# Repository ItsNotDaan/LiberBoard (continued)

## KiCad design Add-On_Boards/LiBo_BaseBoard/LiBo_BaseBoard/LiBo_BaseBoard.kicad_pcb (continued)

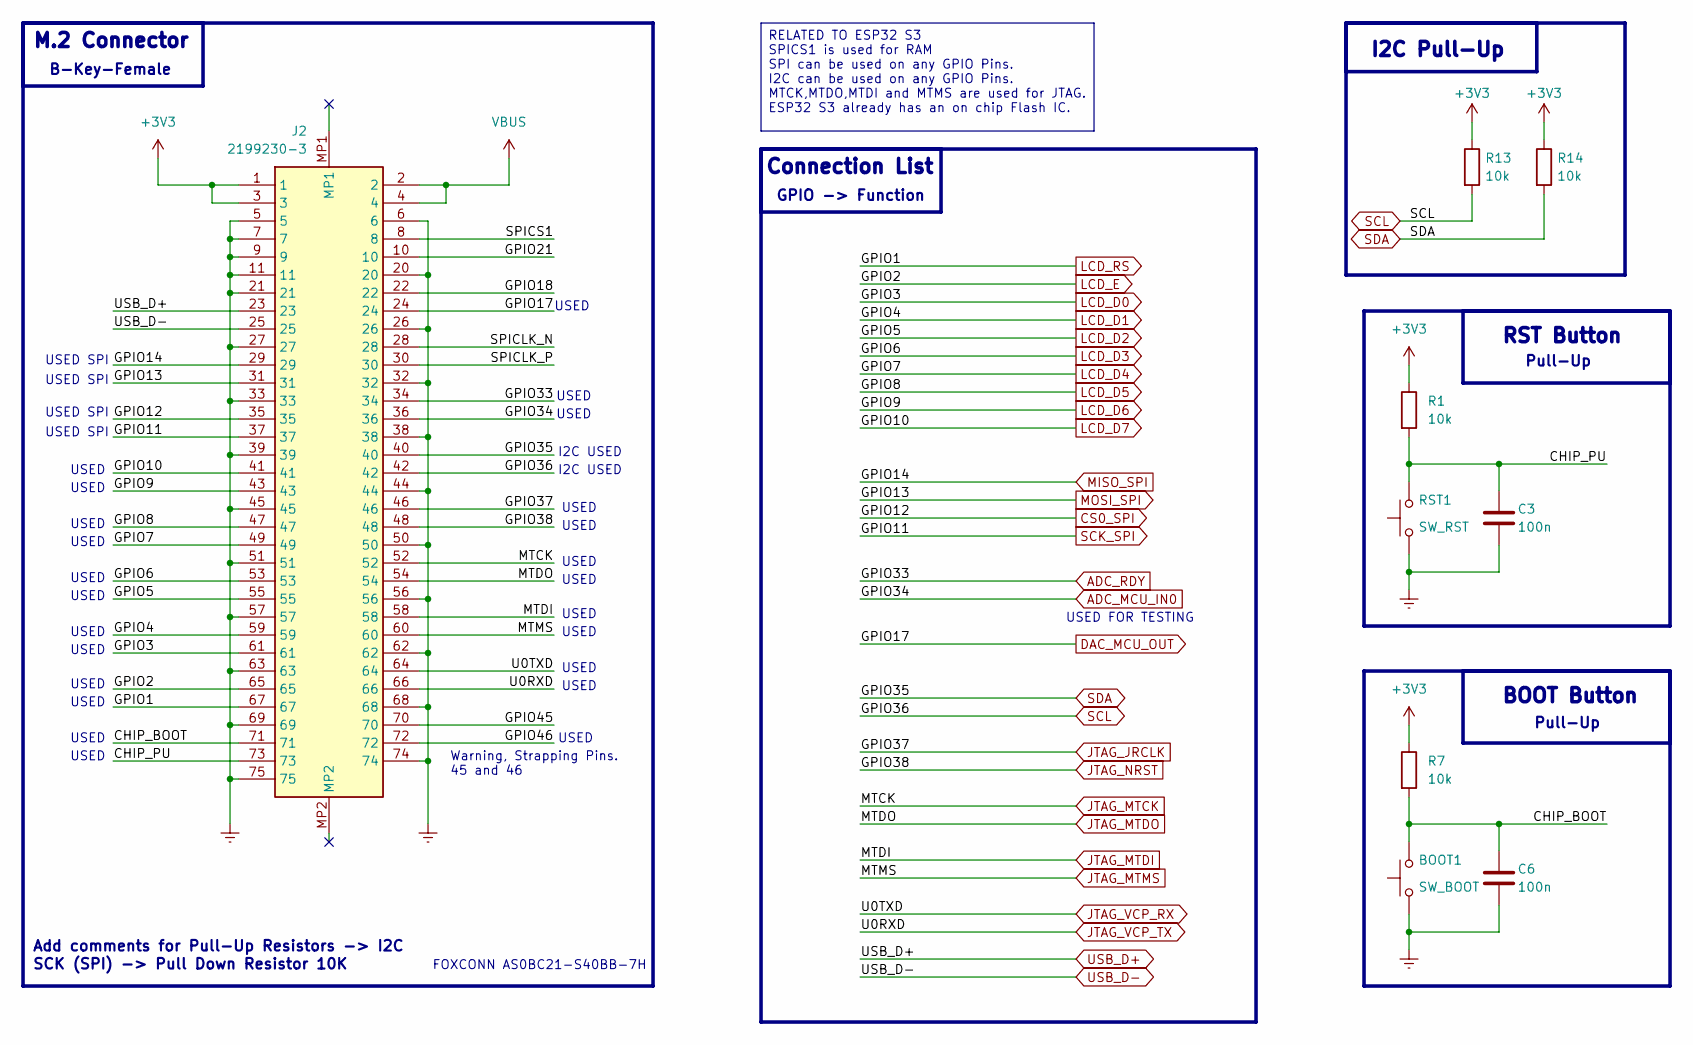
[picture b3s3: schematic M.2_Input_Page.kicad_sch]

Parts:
BOOT1: SW_BOOT; SW_SPST_EVQP2
C3, C6: 100n; C_0805_2012Metric_Pad1.18x1.45mm_HandSolder
J2: 2199230-3; 21992303; Manufacturer_Part_Number 2199230-3
R1, R7, R13, R14: 10k; R_0805_2012Metric_Pad1.20x1.40mm_HandSolder
RST1: SW_RST; SW_SPST_EVQP2

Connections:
+3V3: J2.1, J2.3, R1.1, R7.1, R13.1, R14.1; also elsewhere on the board
/M.2_INPUT/CHIP_BOOT: BOOT1.2, C6.1, J2.71, R7.2
/M.2_INPUT/CHIP_PU: C3.1, J2.73, R1.2, RST1.2
/M.2_INPUT/GPIO18: J2.22
/M.2_INPUT/GPIO21: J2.10
/M.2_INPUT/GPIO45: J2.70
/M.2_INPUT/GPIO46: J2.72
/M.2_INPUT/SPICLK_N: J2.28
/M.2_INPUT/SPICLK_P: J2.30
/M.2_INPUT/SPICS1: J2.8
ADC_MCU_IN0: J2.36; also elsewhere on the board
ADC_RDY: J2.34; also elsewhere on the board
CS0_SPI: J2.35; also elsewhere on the board
DAC_MCU_OUT: J2.24; also elsewhere on the board
Earth: BOOT1.1, C3.2, C6.2, J2.5, J2.6, J2.7, J2.9, J2.11, J2.20, J2.21, J2.26, J2.27, J2.32, J2.33, J2.38, J2.39, J2.44, J2.45, J2.50, J2.51, J2.56, J2.57, J2.62, J2.63, J2.68, J2.69, J2.74, J2.75, RST1.1; also elsewhere on the board
JTAG_JRCLK: J2.46; also elsewhere on the board
JTAG_MTCK: J2.52; also elsewhere on the board
JTAG_MTDI: J2.58; also elsewhere on the board
JTAG_MTDO: J2.54; also elsewhere on the board
JTAG_MTMS: J2.60; also elsewhere on the board
JTAG_NRST: J2.48; also elsewhere on the board
JTAG_VCP_RX: J2.64; also elsewhere on the board
JTAG_VCP_TX: J2.66; also elsewhere on the board
LCD_D0: J2.61
LCD_D1: J2.59
LCD_D2: J2.55
LCD_D3: J2.53
LCD_D4: J2.49
LCD_D5: J2.47
LCD_D6: J2.43
LCD_D7: J2.41
LCD_E: J2.65
LCD_RS: J2.67
MISO_SPI: J2.29; also elsewhere on the board
MOSI_SPI: J2.31; also elsewhere on the board
SCK_SPI: J2.37; also elsewhere on the board
SCL: J2.42, R13.2; also elsewhere on the board
SDA: J2.40, R14.2; also elsewhere on the board
USB_D+: J2.23; also elsewhere on the board
USB_D-: J2.25; also elsewhere on the board
VBUS: J2.2, J2.4; also elsewhere on the board

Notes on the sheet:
USED
BOOT Button
I2C USED
USED SPI
GPIO -> Function
Pull-Up
M.2 Connector
I2C Pull-Up
B-Key-Female
Warning, Strapping Pins. 45 and 46
RST Button
SCK (SPI) -> Pull Down Resistor 10K
Connection List
FOXCONN AS0BC21-S40BB-7H
USED FOR TESTING
Add comments for Pull-Up Resistors -> I2C
RELATED TO ESP32 S3 SPICS1 is used for RAM SPI can be used on any GPIO Pins. I2C can be used on any GPIO Pins. MTCK,MTDO,MTDI and MTMS are used for JTAG. ESP32 S3 already has an on chip Flash IC.

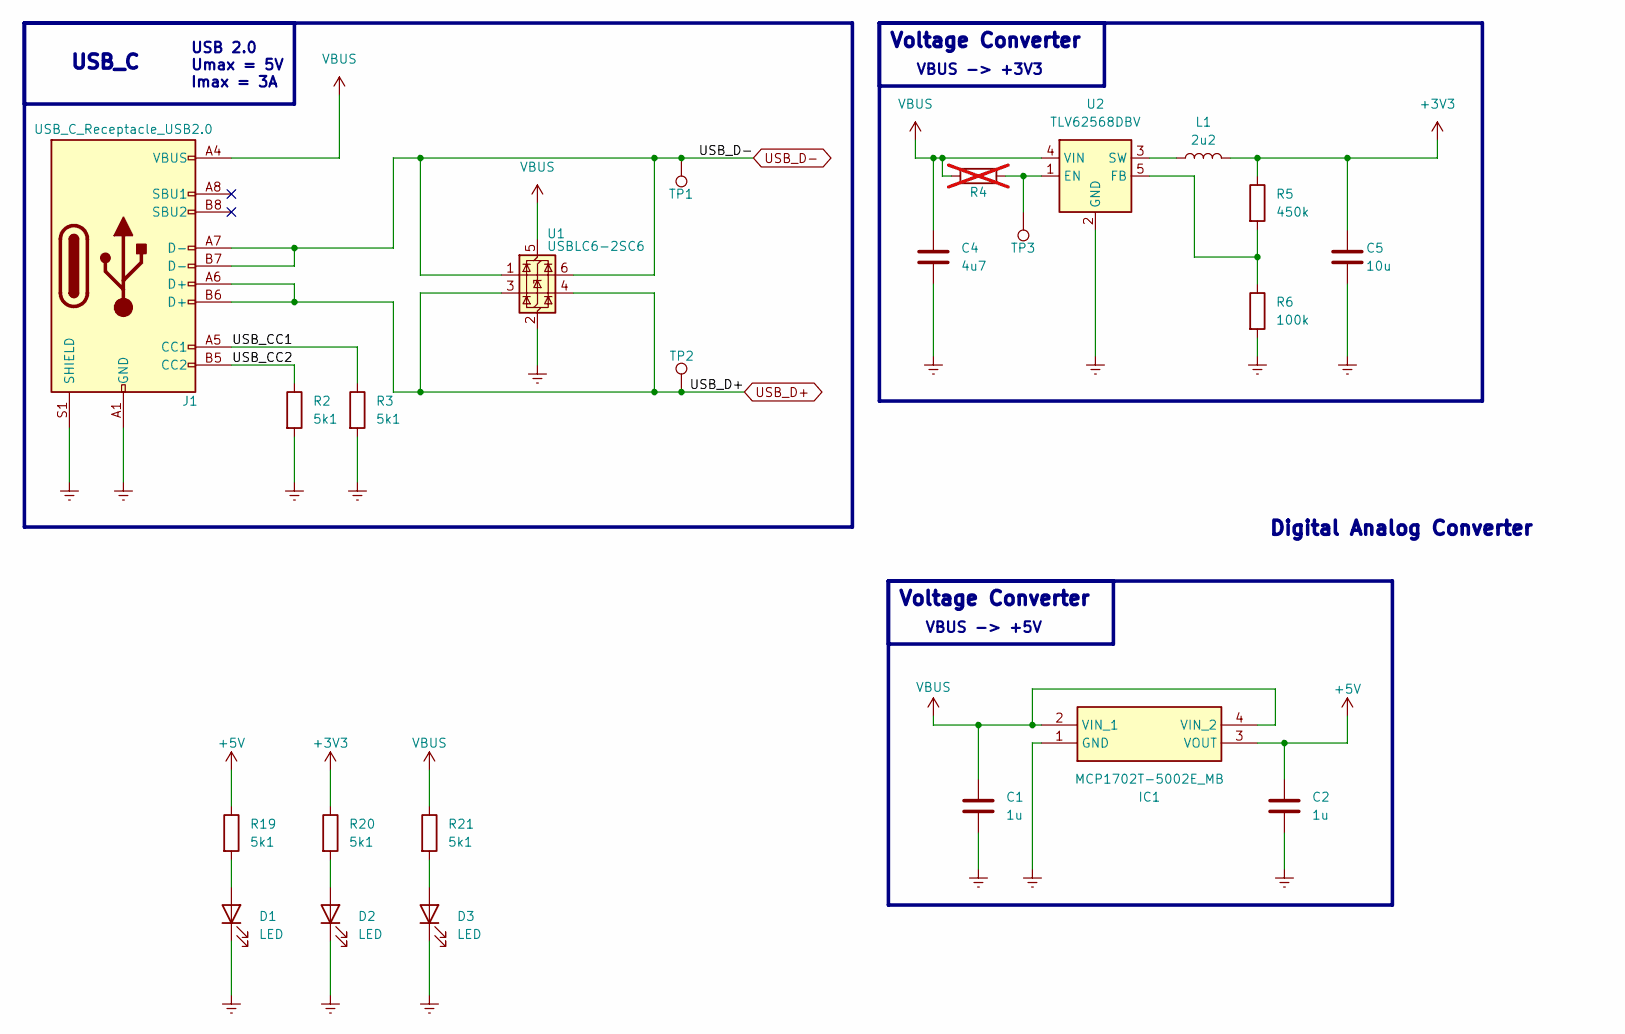
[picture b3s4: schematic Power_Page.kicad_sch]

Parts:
C1, C2: 1u; C_0805_2012Metric_Pad1.18x1.45mm_HandSolder
C4: 4u7; C_0805_2012Metric_Pad1.18x1.45mm_HandSolder
C5: 10u; C_0805_2012Metric_Pad1.18x1.45mm_HandSolder
D1, D2, D3: LED; LED_0805_2012Metric_Pad1.15x1.40mm_HandSolder
IC1: MCP1702T-5002E_MB; MCP1703T5002EMB; Manufacturer_Part_Number MCP1702T-5002E/MB
J1: USB_C_Receptacle_USB2.0; USB_C_Receptacle_GCT_USB4105-xx-A_16P_TopMnt_Horizontal
L1: 2u2; LED_0805_2012Metric_Pad1.15x1.40mm_HandSolder
R2, R3, R19, R20, R21: 5k1; R_0805_2012Metric_Pad1.20x1.40mm_HandSolder
R4: 10k; R_0805_2012Metric_Pad1.20x1.40mm_HandSolder; not fitted
R5: 450k; R_0805_2012Metric_Pad1.20x1.40mm_HandSolder
R6: 100k; R_0805_2012Metric_Pad1.20x1.40mm_HandSolder
TP1, TP2, TP3: TestPoint; TestPoint_Pad_D1.0mm
U1: USBLC6-2SC6; SOT-23-6
U2: TLV62568DBV; SOT-23-5

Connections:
+3V3: C5.1, L1.2, R5.1, R20.1; also elsewhere on the board
+5V: C2.1, IC1.3 (VOUT), R19.1; also elsewhere on the board
/POWER/USB_CC1: J1.A5 (CC1), R3.1
/POWER/USB_CC2: J1.B5 (CC2), R2.1
Earth: C1.2, C2.2, C4.2, C5.2, D1.1 (K), D2.1 (K), D3.1 (K), IC1.1 (GND), J1.A1 (GND), J1.A12 (GND), J1.B1 (GND), J1.B12 (GND), J1.S1 (SHIELD), R2.2, R3.2, R6.2, U1.2 (GND), U2.2 (GND); also elsewhere on the board
unnamed: D1.2 (A), R19.2
unnamed: D2.2 (A), R20.2
unnamed: D3.2 (A), R21.2
unnamed: R4.2, TP3.1, U2.1 (EN)
unnamed: R5.2, R6.1, U2.5 (FB)
unnamed: L1.1, U2.3 (SW)
USB_D+: J1.A6 (D+), J1.B6 (D+), TP2.1, U1.3 (I/O2), U1.4 (I/O2); also elsewhere on the board
USB_D-: J1.A7 (D-), J1.B7 (D-), TP1.1, U1.1 (I/O1), U1.6 (I/O1); also elsewhere on the board
VBUS: C1.1, C4.1, IC1.2 (VIN_1), IC1.4 (VIN_2), J1.A4 (VBUS), J1.A9 (VBUS), J1.B4 (VBUS), J1.B9 (VBUS), R4.1, R21.1, U1.5 (VBUS), U2.4 (VIN); also elsewhere on the board

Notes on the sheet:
VBUS -> +3V3
Voltage Converter
VBUS -> +5V
USB 2.0 Umax = 5V Imax = 3A
Digital Analog Converter
USB_C

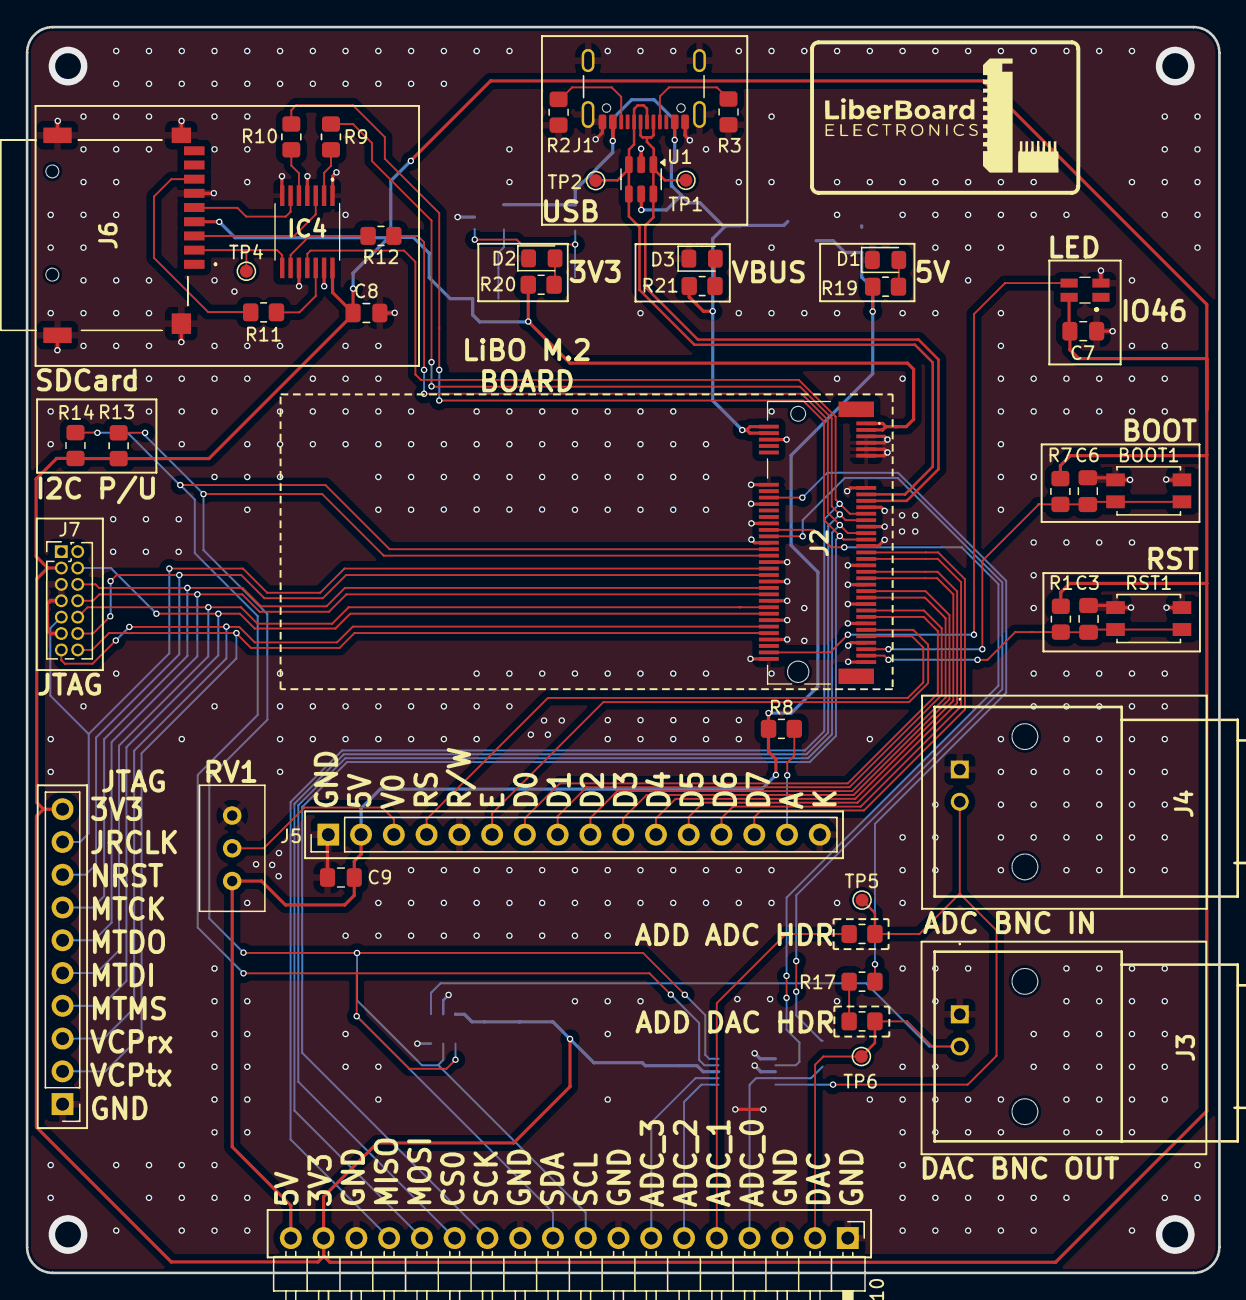
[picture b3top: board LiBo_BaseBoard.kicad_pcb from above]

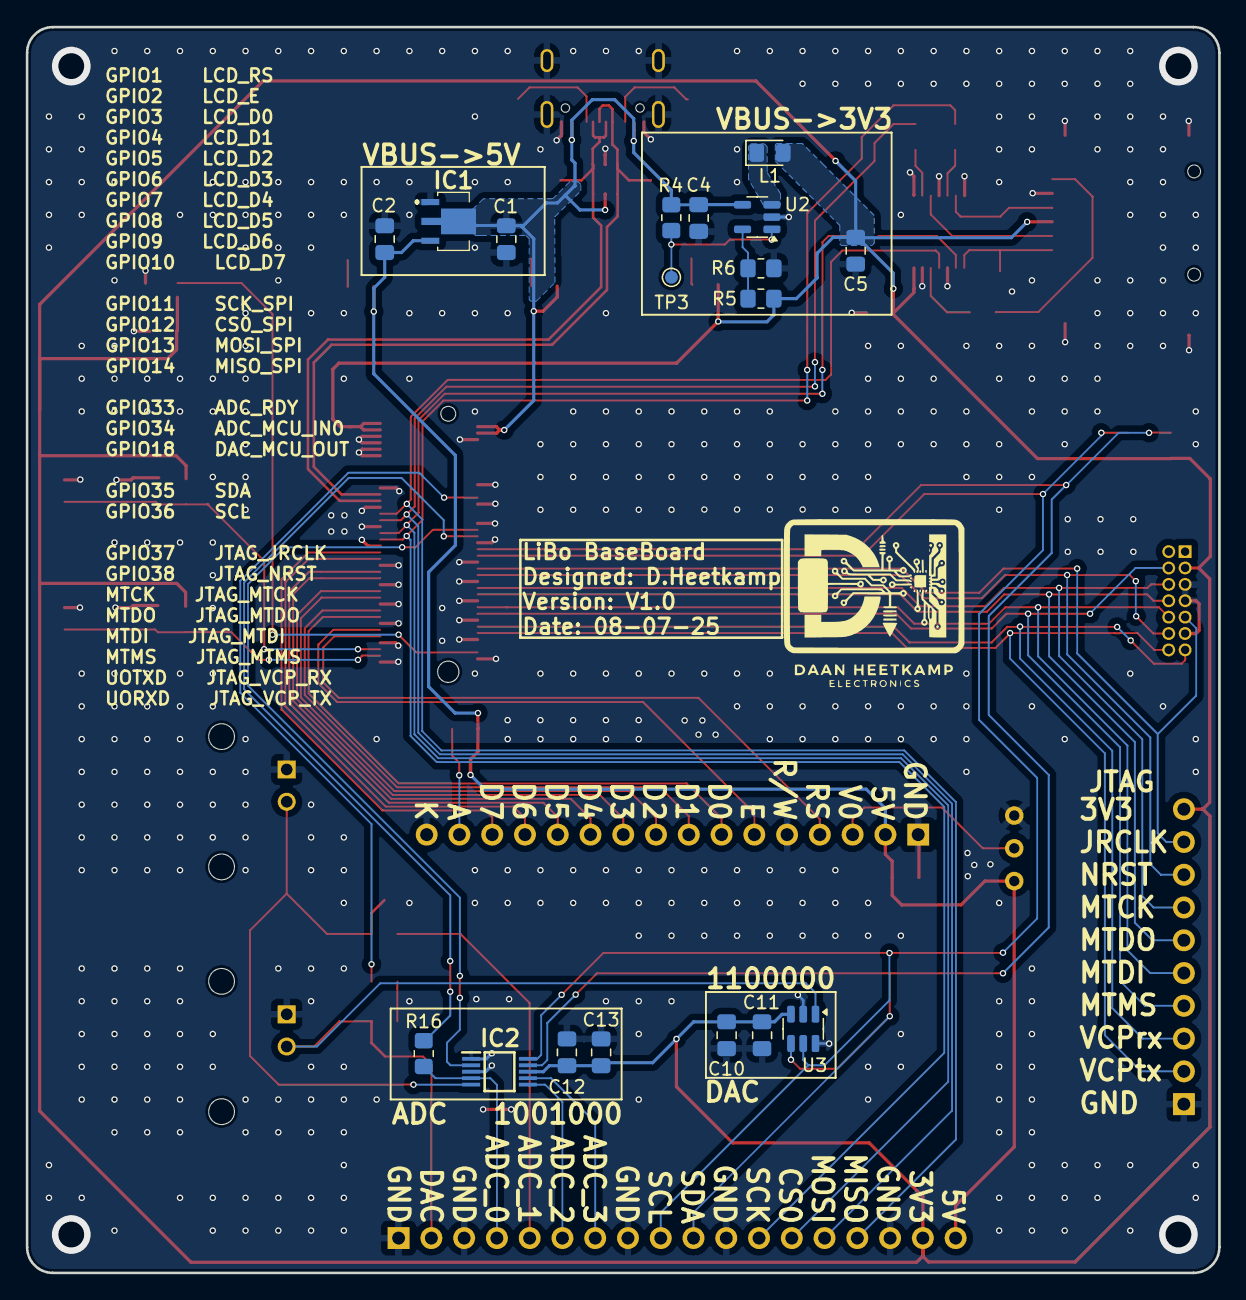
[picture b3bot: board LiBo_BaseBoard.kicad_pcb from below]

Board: 2 copper layers, 92.4 x 96.6 mm, 63 parts (18 on the bottom side), 50 nets.

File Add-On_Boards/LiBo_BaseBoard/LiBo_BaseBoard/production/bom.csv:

Designator,Footprint,Quantity,Value,LCSC Part #
"_2, ",,2,,
BOOT1,SW_SPST_EVQP2,1,SW_BOOT,
"C1, C2",0805,2,1u,
"C10, C13, C5",0805,3,10u,
"C11, C12, C3, C6, C7, C8",0805,6,100n,
"C4, C9",0805,2,4u7,
"D1, D2, D3",0805,3,LED,
IC1,MCP1703T5002EMB,1,MCP1702T-5002E_MB,
IC2,SOP50P490X110-10N,1,ADS1015IDGSR,
IC4,SN74LVC125APWR,1,SN74LVC125APWR,
J1,USB_C_Receptacle_GCT_USB4105-xx-A_16P_TopMnt_Horizontal,1,USB_C_Receptacle_USB2.0,
J10,PinHeader_1x18_P2.54mm_Horizontal,1,Conn_01x18,
J2,21992303,1,2199230-3,
"J3, J4",KHBNC503511,2,KH-BNC50-3511,
J5,PinHeader_1x16_P2.54mm_Vertical,1,Conn_01x16,
J6,TFPUSH,1,TF_PUSH,
J7,PinHeader_2x07_P1.27mm_Vertical,1,Conn_ST_STDC14,
J8,PinHeader_1x10_P2.54mm_Vertical,1,Conn_01x10,
L1,0805,1,2u2,
LED1,WS2812C2020,1,WS2812C-2020,
"R1, R13, R14, R7",0805,4,10k,
"R10, R11, R12, R16, R17, R9",0805,6,3k3,
"R19, R2, R20, R21, R3",0805,5,5k1,
R5,0805,1,450k,
R6,0805,1,100k,
R8,0805,1,220,
RST1,SW_SPST_EVQP2,1,SW_RST,
RV1,Potentiometer_Bourns_3296W_Vertical,1,10k,
U1,SOT-23-6,1,USBLC6-2SC6,
U2,SOT-23-5,1,TLV62568DBV,
U3,SOT-23-6,1,MCP4725A0T-E/CH,

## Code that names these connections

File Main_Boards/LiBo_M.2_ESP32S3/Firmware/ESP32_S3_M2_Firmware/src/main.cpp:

#include <Arduino.h>
// #include <LED.h>

/*To do:
  - Add the SPI flash memory. DONE
  - Add the RGB LED. DONE
  - Check the USB connection.
  - Add some DSP functions in Espressif IoT Development Framework.
  - Add a WiFi connection.
  - Add a Bluetooth connection.

*/

// #include <FastLED.h>

// #define DATA_PIN 46
// #define NUM_LEDS 1
// #define BRIGHTNESS 30
// #define LED_TYPE WS2812B
// #define COLOR_ORDER RGB

// // Declare the array of leds
// CRGB leds[NUM_LEDS];

// #define UPDATES_PER_SECOND 100

// void RGB_LED(bool state, int r, int g, int b)
// {
//   if (state)
//   {
//     leds[0] = CRGB(r, g, b);
//     FastLED.show();
//   }
//   else
//   {
//     leds[0] = CRGB(0, 0, 0);
//     FastLED.show();
//   }
// }

void setup()
{
  // put your setup code here, to run once:

  Serial.begin(115200);
  delay(1000); // Allow time for Serial to initialize
  Serial.println("\n\nSetup starting...");

  // Init LED
  // Serial.println("Initializing FastLED...");
  // FastLED.addLeds<LED_TYPE, DATA_PIN, COLOR_ORDER>(leds, NUM_LEDS);
  // FastLED.setBrightness(BRIGHTNESS);
  // Serial.println("FastLED initialized successfully");
}

void loop()
{
  // put your main code here, to run repeatedly:

  Serial.println("LED ON");
  // RGB_LED(true, 255, 0, 0);
  delay(1000);

  Serial.println("LED OFF");
  // RGB_LED(false, 0, 0, 0);
  delay(1000);
}

// ESP32S3 PINS	ESP32S3 PIN_FUNCT	USED_PINS	M.2_USED_PINS	EXTRA_INFORMATION
// 1	LNA_IN	-	-	-
// 2	VDD3P3	-	-	-
// 3	VDD3P3	-	-	-
// 4	CHIP_PU	CHIP_PU	73	-
// 5	GPIO0	CHIP_BOOT	71	-
// 6	GPIO1	GPIO1	67	-
// 7	GPIO2	GPIO2	65	-
// 8	GPIO3	GPIO3	61	-
// 9	GPIO4	GPIO4	59	-
// 10	GPIO5	GPIO5	55	-
// 11	GPIO6	GPIO6	53	-
// 12	GPIO7	GPIO7	49	-
// 13	GPIO8	GPIO8	47	-
// 14	GPIO9	GPIO9	43	-
// 15	GPIO10	GPIO10	41	-
// 16	GPIO11	GPIO11	37	-
// 17	GPIO12	GPIO12	35	-
// 18	GPIO13	GPIO13	31	-
// 19	GPIO14	GPIO14	29	-
// 20	VDD3P3_RTC	-	-	-
// 21	XTAL_32K_P	-	-	-
// 22	XTAL_32K_N	-	-	-
// 23	GPIO17	GPIO17	24	-
// 24	GPIO18	GPIO18	22	-
// 25	GPIO19/USB_D-	USB_D-	25	Solder_Pad
// 26	GPIO20/USB_D+	USB_D+	23	Solder_Pad
// 27	GPIO21	GPIO21	10	-
// 28	SPICS1	SPICS1	8	-
// 29	VDD_SPI	-	-	-
// 30	SPIHD	-	-	-
// 31	SPIWP	-	-	-
// 32	SPICS0	-	-	-
// 33	SPICLK	-	-	-
// 34	SPIQ	-	-	-
// 35	SPID	-	-	-
// 36	SPICLK_N	SPICLK_N	28	-
// 37	SPICLK_P	SPICLK_P	30	-
// 38	GPIO33	GPIO33	34	-
// 39	GPIO34	GPIO34	36	-
// 40	GPIO35	GPIO35	40	-
// 41	GPIO36	GPIO36	42	-
// 42	GPIO37	GPIO37	46	-
// 43	GPIO38	GPIO38	48	-
// 44	MTCK	MTCK	53	-
// 45	MTDO	MTDO	54	-
// 46	VDD3P3_CPU	-	-	-
// 47	MTDI	MTDI	58	-
// 48	MTMS	MTMS	60	-
// 49	U0TXD	U0TXD	64	-
// 50	U0RXD	U0RXD	66	-
// 51	GPIO45	GPIO45	70	Pull_Up_Res/Strapping Pins
// 52	GPIO46	GPIO46	72	RGB_LED
// 53	XTAL_N	-	-	-
// 54	XTAL_P	-	-	-
// 55	VDDA	-	-	-
// 56	VDDA	-	-	-
// 57	GND	-	-	-

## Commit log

2024-05-07 Create licence CERN-OHL-P
2024-05-07 Rename licence to LICENCE
2024-05-07 Create MainBoards
2024-05-07 Changed the folder distrubution for the main boards
2024-05-07 Added Add On Boards
2024-05-07 feat: added readme for all the boards
2024-05-07 feat: Added main readme
2024-05-08 feat: added lib and arduino board
2024-05-08 fix:edit
2024-05-08 Changed library in the submodule for tests
2024-05-08 Changes to ArduinoBoard
    Needed:
    1. Diodes.
    2. Status LEDS
    3. Footprint checking
2024-05-29 Arduino + Base
    Arduino needs to be finished.
    Base schematic almost done.
2024-05-30 Finish Schem - Begin Layout
2024-06-03 Added stuff
2024-06-04 Improved the layout
2024-06-06 Almost finished layout - BaseBoard
2024-07-18 Baseboard done
2025-03-01 Feat: LiBo_M.2_ESP32S3 Added
2025-03-01 Updated libs
2025-07-08 updated the Libo M.2 main board
2025-08-29 first release
2025-12-21 Add positions.csv for ESP32S3 M.2 Board with component placements and orientations
2026-04-19 Add new STEP and WRL files for M.2 Arduino and ESP32S3 Boards
    - Added M.2 Arduino Module Board STEP file (12633 KB)
    - Added ESP32S3 M.2 Board STEP file (16645 KB)
    - Added WRL file for unnamed ESP32S3 M.2 Board (2692 KB)
    - Created lock file for ESP32S3 M.2 Board project
2026-04-19 edit
2026-04-30 This is a 3d addage
